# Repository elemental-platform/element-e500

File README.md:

# element-e500
Wireless door/window monitor (reed switch) based on RFM69 radio

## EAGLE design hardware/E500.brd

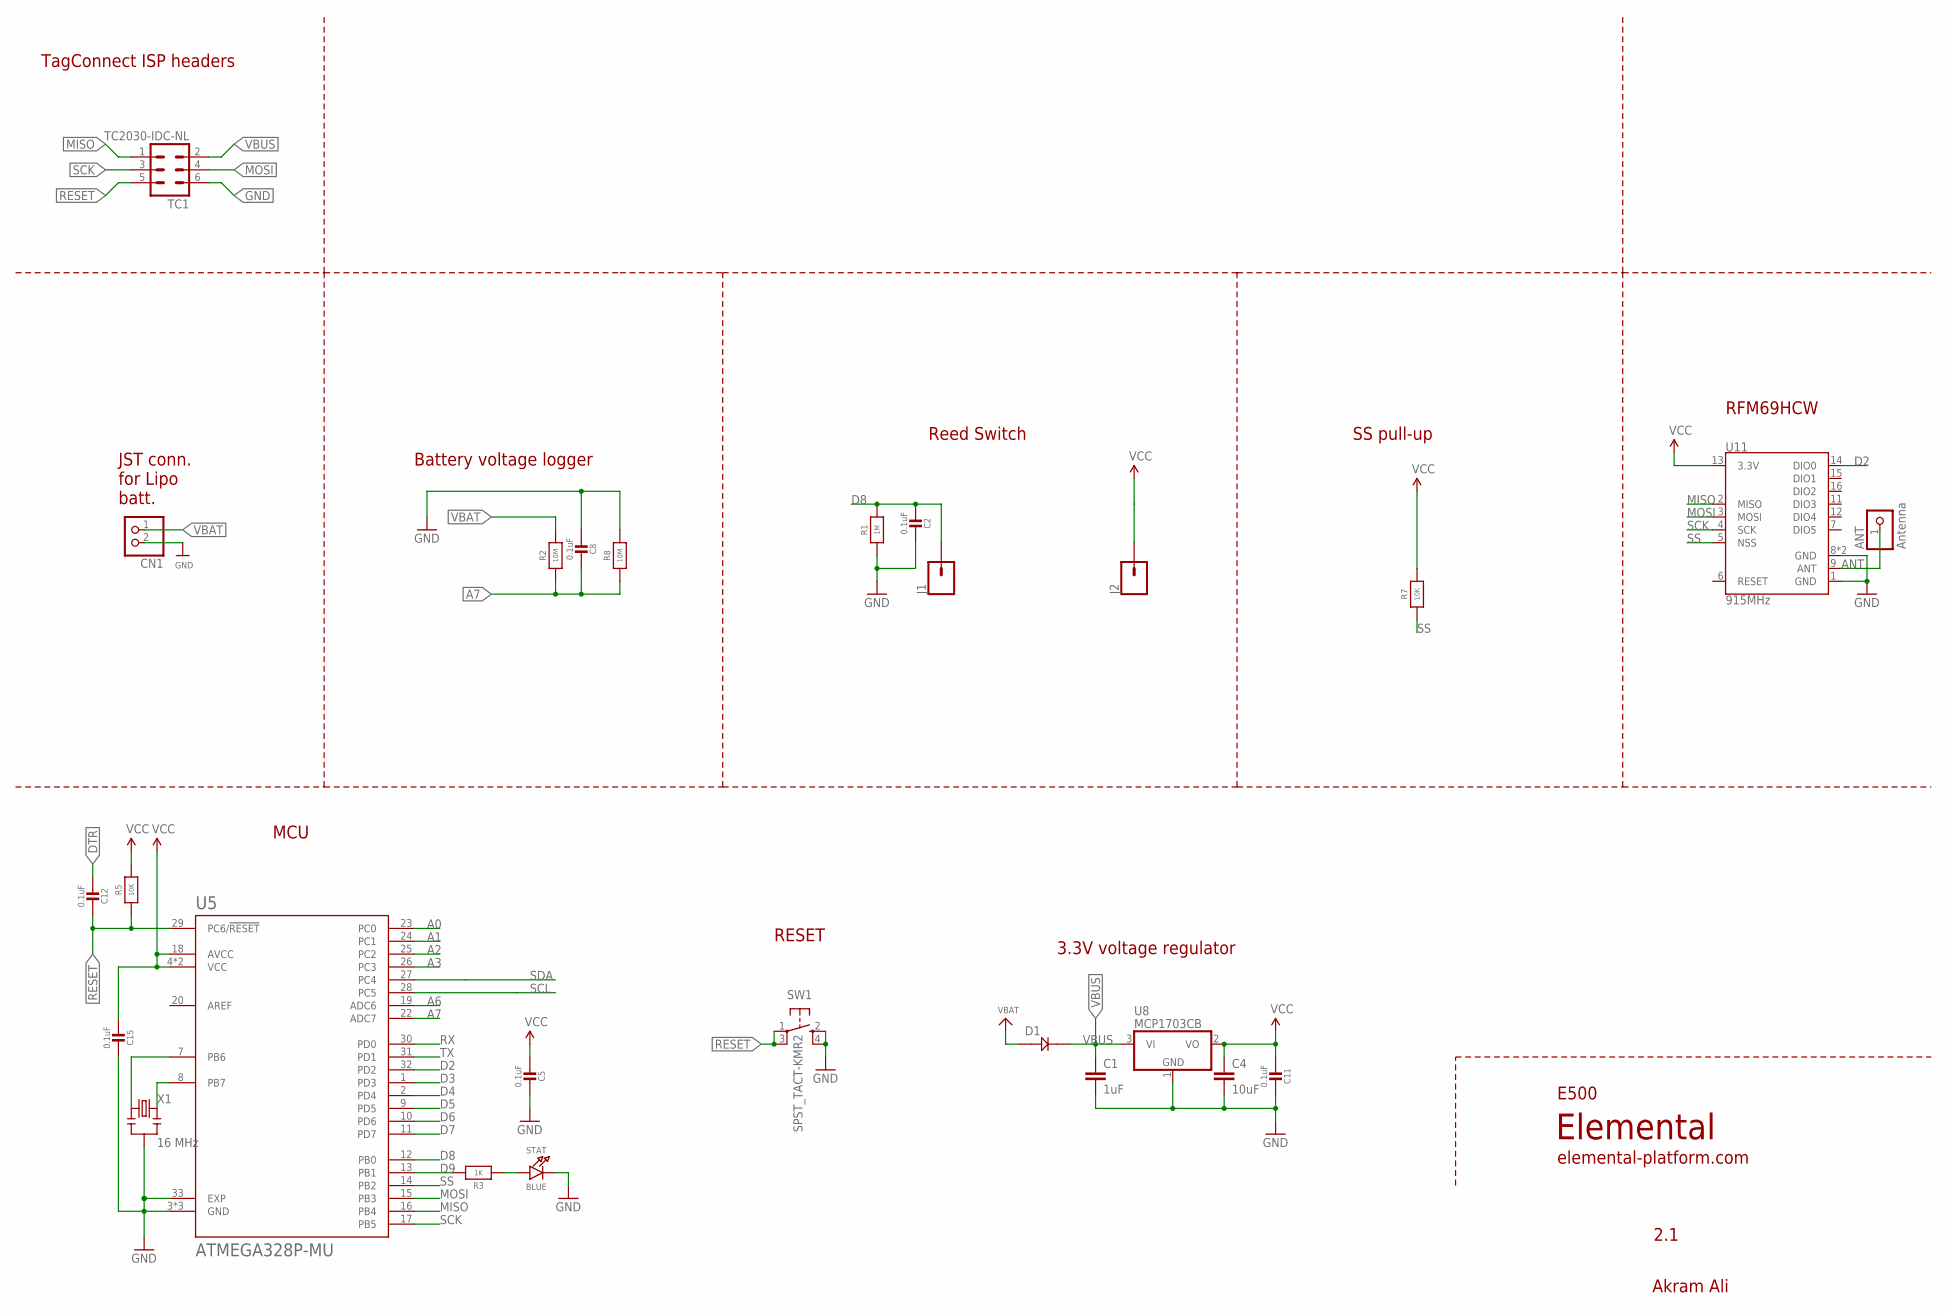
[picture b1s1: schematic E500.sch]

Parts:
ANT: Antenna; 1X01-CLEANBIG; MPN Helical antenna
C1: 1uF; 0805; MPN CC0805ZRY5V8BB105
C2, C5, C8, C11, C12, C15: 0.1uF; MICROBUILDER__0402MP; MPN GRM155R71C104KA88J
C4: 10uF; 0805; MPN CC0805KKX5R6BB106
CN1: JST_2PIN-SMT-RA; JST-PH-2-SMT-RA
D1: DIODE_SCHOTTKY0805-RES; 0805
J1, J2: CONN_01; 1X01
R1: 1M; MICROBUILDER__0402MP; MPN RC0402JR-0710KL
R2, R8: 10M; MICROBUILDER__0402MP; MPN RC0402JR-0710KL
R3: 1K; MICROBUILDER__0402MP; MPN RC0402JR-0710KL
R5, R7: 10K; MICROBUILDER__0402MP; MPN RC0402JR-0710KL
STAT: BLUE; CHIPLED_0805_NOOUTLINE
SW1: SPST_TACT-KMR2; KMR2
TC1: TC2030-IDC-NL
U5: ATMEGA328P-MU; QFN50P500X500X100-33N; MPN ATMEGA328P-MU
U8: MCP1703CB; SOT23; MPN MCP1703T-3302E/CB
U11: 915MHz; RFM69HCW-XXXS2; MPN RFM69HCW
X1: 16 MHz; RESONATOR-SMD; MPN CSTCE16M0V53-R0

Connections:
A0: U5.23 (PC0)
A1: U5.24 (PC1)
A2: U5.25 (PC2)
A3: U5.26 (PC3)
A6: U5.19 (ADC6)
A7: C8.1, R2.1, R8.1, U5.22 (ADC7)
ANT: ANT.1, U11.9 (ANT)
D2: U5.32 (PD2), U11.14 (DIO0)
D3: U5.1 (PD3)
D4: U5.2 (PD4)
D5: U5.9 (PD5)
D6: U5.10 (PD6)
D7: U5.11 (PD7)
D8: C2.2, J1.1, R1.2, U5.12 (PB0)
D9: R3.2, U5.13 (PB1)
DTR: C12.2
GND: C1.2, C2.1, C4.2, C5.1, C8.2, C11.1, C15.1, CN1.2 (1), R1.1, R8.2, STAT.C, SW1.2 (S), SW1.4 (S1), TC1.6, U5.3 (GND), U5.5 (GND), U5.21 (GND), U5.33 (EXP), U8.1 (GND), U11.1 (GND), U11.8 (GND), U11.10 (GND), X1.2
MISO: TC1.1, U5.16 (PB4), U11.2 (MISO)
MOSI: TC1.4, U5.15 (PB3), U11.3 (MOSI)
unnamed: U5.8 (PB7), X1.3
unnamed: U5.7 (PB6), X1.1
unnamed: R3.1, STAT.A
RESET: C12.1, R5.1, SW1.1, SW1.3 (P1), TC1.5, U5.29 (PC6/!RESET)
RX: U5.30 (PD0)
SCK: TC1.3, U5.17 (PB5), U11.4 (SCK)
SCL: U5.28 (PC5)
SDA: U5.27 (PC4)
SS: R7.1, U5.14 (PB2), U11.5 (NSS)
TX: U5.31 (PD1)
VBAT: CN1.1 (2), D1.1, R2.2
VBUS: C1.1, D1.2, TC1.2, U8.3 (VI)
VCC: C4.1, C5.2, C11.2, C15.2, J2.1, R5.2, R7.2, U5.4 (VCC), U5.6 (VCC), U5.18 (AVCC), U8.2 (VO), U11.13 (3.3V)

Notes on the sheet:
TagConnect ISP headers
3.3V voltage regulator
Elemental
E500
Akram Ali
2.1
elemental-platform.com
RFM69HCW
MCU
RESET
Battery voltage logger
JST conn. for Lipo batt.
SS pull-up
Reed Switch

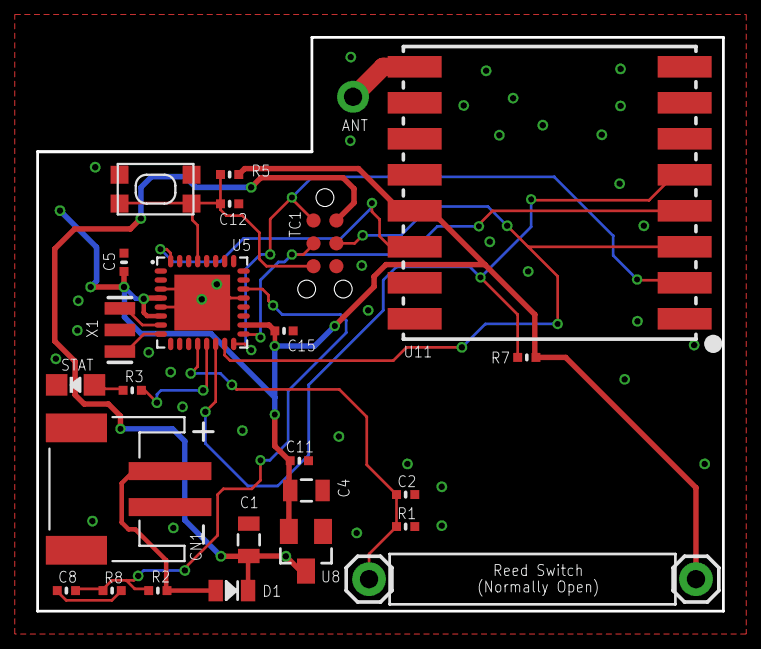
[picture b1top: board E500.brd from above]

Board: 2 copper layers, 38.1 x 31.9 mm, 26 parts (0 on the bottom side), 17 nets.

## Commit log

2019-09-02 Create LICENSE
2019-10-17 v2.2 - minor update
    - removed solder jumper from SS pin
    - added bottom silkscreen for node id
    - DRU mask limit to 14mil for covering via with solder mask
    - very minor trace adjustment
    - functionally same as previous
2019-12-23 Update firmware.ino
    removed node ID from datapacket (gateway already has it in the encrypted packet, so it can retrieve it directly)
2020-01-30 changed freq, encrypt and org
    - changed exact frequency to 905MHz
    - changed encrypt key
    - reorganized code and cleaned up
    - reduced some delays

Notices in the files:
parts and their libraries:
SparkFun-Capacitors: Licensing: Creative Commons ShareAlike 4.0 International - https://creativecommons.org/licenses/by-sa/4.0
microbuilder: This work is placed in the public domain, and may be freely used for commercial and non-commercial work with the following conditions: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
